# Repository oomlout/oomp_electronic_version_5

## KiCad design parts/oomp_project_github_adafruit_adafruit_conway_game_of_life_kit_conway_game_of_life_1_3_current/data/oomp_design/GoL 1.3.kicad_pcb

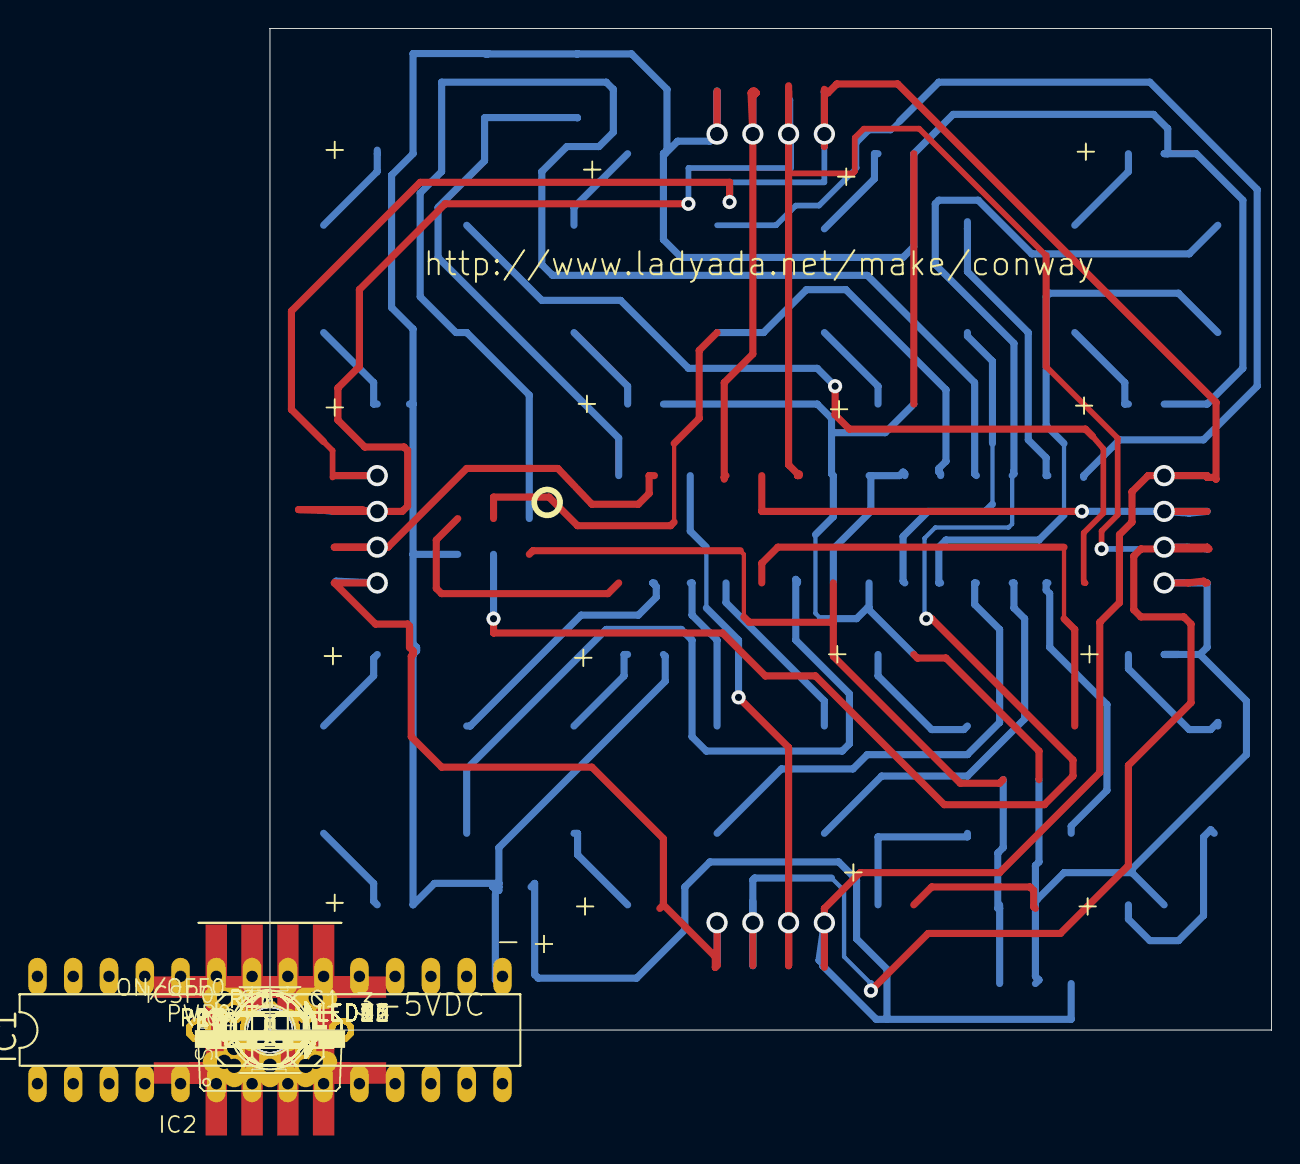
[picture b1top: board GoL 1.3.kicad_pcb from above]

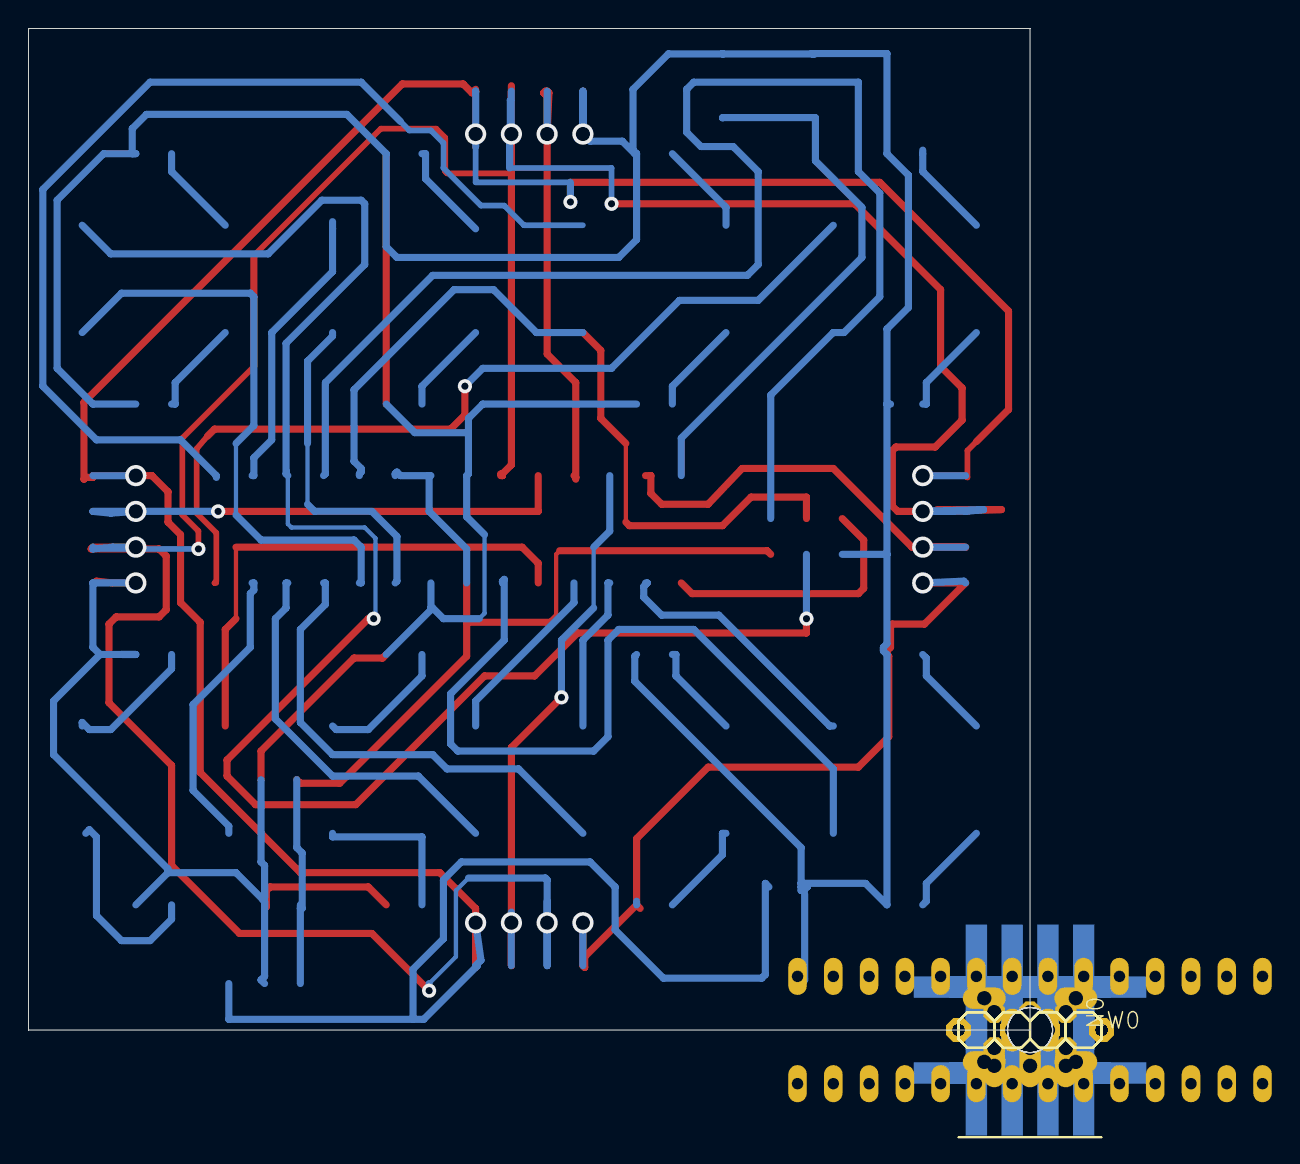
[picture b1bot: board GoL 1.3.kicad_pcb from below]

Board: 16 copper layers, 71.1 x 71.1 mm, 48 parts (2 on the bottom side), 42 nets.

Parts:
C1: 100uF; E2,5-6
C2, C3: 0.1uF; C025-025X050
E0: CONNECT4; http___www.ladyada.net_make_conway_2
IC1: ATMEGA48-10PI; _b_Dual In-line Package__b_ - 28 pin
IC2: LM7805; http___www.ladyada.net_make_conway
ICSP0: 2X03
LED1, LED2, LED3, LED4, LED5, LED6, LED7, LED8, LED9, LED10, LED11, LED12, LED13, LED14, LED15, LED16: LED5MM-EZ
N0: CONNECT4; http___www.ladyada.net_make_conway_2
ON/OFF0: B3F-10XX
PWR0: 1X02
R1, R2, R3, R4, R5, R6, R7, R8, R9, R10, R11, R12, R13, R14, R15, R16: 0207_10
S0: CONNECT4; http___www.ladyada.net_make_conway_2
UNK_HOLE_0: dummyfp0
UNK_HOLE_1: dummyfp1
UNK_HOLE_2: dummyfp2
UNK_HOLE_3: dummyfp3
W0: CONNECT4; http___www.ladyada.net_make_conway_2

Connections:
+5V: C1.+, C3.1, IC1.7, IC1.20, IC1.21, IC2.3, ICSP0.2
BCAST: E0.B3, E0.F3, IC1.23, N0.B2, N0.F2, S0.B3, S0.F3, W0.B2, W0.F2
ERX: E0.B2, E0.F2, IC1.24
GND: C1.-, C2.2, C3.2, E0.B4, E0.F4, IC1.8, IC1.22, IC2.2, ICSP0.6, LED1.K, LED2.K, LED3.K, LED4.K, LED5.K, LED6.K, LED7.K, LED8.K, LED9.K, LED10.K, LED11.K, LED12.K, LED13.K, LED14.K, LED15.K, LED16.K, N0.B4, N0.F4, ON/OFF0.3, ON/OFF0.4, PWR0.2, S0.B4, S0.F4, W0.B4, W0.F4
MISO: IC1.18, ICSP0.1, R5.1
MOSI: IC1.17, ICSP0.4, R4.1
unnamed: LED1.A, R1.2
unnamed: LED2.A, R2.2
unnamed: LED3.A, R3.2
unnamed: LED4.A, R4.2
unnamed: LED5.A, R5.2
unnamed: LED6.A, R6.2
unnamed: LED7.A, R7.2
unnamed: LED8.A, R8.2
unnamed: LED9.A, R9.2
unnamed: LED10.A, R10.2
unnamed: LED11.A, R11.2
unnamed: LED12.A, R12.2
unnamed: LED13.A, R13.2
unnamed: LED14.A, R14.2
unnamed: LED15.A, R15.2
unnamed: LED16.A, R16.2
unnamed: IC1.13, R16.1
unnamed: IC1.12, R15.1
unnamed: IC1.11, R14.1
unnamed: IC1.6, R13.1
unnamed: IC1.5, R12.1
unnamed: IC1.4, R11.1
unnamed: IC1.3, R10.1
unnamed: IC1.2, R9.1
unnamed: IC1.28, ON/OFF0.1, ON/OFF0.2
unnamed: IC1.14, R1.1
unnamed: IC1.15, R2.1
unnamed: IC1.16, R3.1
unnamed: IC1.9, R7.1
unnamed: IC1.10, R8.1
NRX: IC1.25, N0.B3, N0.F3
RESET: IC1.1, ICSP0.5
SCK: IC1.19, ICSP0.3, R6.1
SRX: IC1.26, S0.B2, S0.F2
V+: C2.1, E0.B1, E0.F1, IC2.1, N0.B1, N0.F1, PWR0.1, S0.B1, S0.F1, W0.B1, W0.F1
WRX: IC1.27, W0.B3, W0.F3

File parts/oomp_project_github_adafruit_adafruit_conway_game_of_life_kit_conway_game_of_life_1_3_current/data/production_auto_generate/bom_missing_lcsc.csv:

Designator,Comment,Footprint,OOMP ID,Reason
C1,100uF,"GoL 1.3-import-fps:E2,5-6",,No verified LCSC part number
C2,0.1uF,GoL 1.3-import-fps:C025-025X050,,No verified LCSC part number
C3,0.1uF,GoL 1.3-import-fps:C025-025X050,,No verified LCSC part number
E0,CONNECT4,GoL 1.3-import-fps:http___www.ladyada.net_make_conway_2,,No verified LCSC part number
IC1,ATMEGA48-10PI,GoL 1.3-import-fps:_b_Dual In-line Package__b_ - 28 pin,,No verified LCSC part number
IC2,LM7805,GoL 1.3-import-fps:http___www.ladyada.net_make_conway,,No verified LCSC part number
ICSP0,,GoL 1.3-import-fps:2X03,,No verified LCSC part number
LED1,,GoL 1.3-import-fps:LED5MM-EZ,,No verified LCSC part number
LED2,,GoL 1.3-import-fps:LED5MM-EZ,,No verified LCSC part number
LED3,,GoL 1.3-import-fps:LED5MM-EZ,,No verified LCSC part number
LED4,,GoL 1.3-import-fps:LED5MM-EZ,,No verified LCSC part number
LED5,,GoL 1.3-import-fps:LED5MM-EZ,,No verified LCSC part number
LED6,,GoL 1.3-import-fps:LED5MM-EZ,,No verified LCSC part number
LED7,,GoL 1.3-import-fps:LED5MM-EZ,,No verified LCSC part number
LED8,,GoL 1.3-import-fps:LED5MM-EZ,,No verified LCSC part number
LED9,,GoL 1.3-import-fps:LED5MM-EZ,,No verified LCSC part number
LED10,,GoL 1.3-import-fps:LED5MM-EZ,,No verified LCSC part number
LED11,,GoL 1.3-import-fps:LED5MM-EZ,,No verified LCSC part number
LED12,,GoL 1.3-import-fps:LED5MM-EZ,,No verified LCSC part number
LED13,,GoL 1.3-import-fps:LED5MM-EZ,,No verified LCSC part number
LED14,,GoL 1.3-import-fps:LED5MM-EZ,,No verified LCSC part number
LED15,,GoL 1.3-import-fps:LED5MM-EZ,,No verified LCSC part number
LED16,,GoL 1.3-import-fps:LED5MM-EZ,,No verified LCSC part number
N0,CONNECT4,GoL 1.3-import-fps:http___www.ladyada.net_make_conway_2,,No verified LCSC part number
ON/OFF0,,GoL 1.3-import-fps:B3F-10XX,,No verified LCSC part number
PWR0,,GoL 1.3-import-fps:1X02,,No verified LCSC part number
R1,,GoL 1.3-import-fps:0207_10,,No verified LCSC part number
R2,,GoL 1.3-import-fps:0207_10,,No verified LCSC part number
R3,,GoL 1.3-import-fps:0207_10,,No verified LCSC part number
R4,,GoL 1.3-import-fps:0207_10,,No verified LCSC part number
R5,,GoL 1.3-import-fps:0207_10,,No verified LCSC part number
R6,,GoL 1.3-import-fps:0207_10,,No verified LCSC part number
R7,,GoL 1.3-import-fps:0207_10,,No verified LCSC part number
R8,,GoL 1.3-import-fps:0207_10,,No verified LCSC part number
R9,,GoL 1.3-import-fps:0207_10,,No verified LCSC part number
R10,,GoL 1.3-import-fps:0207_10,,No verified LCSC part number
R11,,GoL 1.3-import-fps:0207_10,,No verified LCSC part number
R12,,GoL 1.3-import-fps:0207_10,,No verified LCSC part number
R13,,GoL 1.3-import-fps:0207_10,,No verified LCSC part number
R14,,GoL 1.3-import-fps:0207_10,,No verified LCSC part number
R15,,GoL 1.3-import-fps:0207_10,,No verified LCSC part number
R16,,GoL 1.3-import-fps:0207_10,,No verified LCSC part number
S0,CONNECT4,GoL 1.3-import-fps:http___www.ladyada.net_make_conway_2,,No verified LCSC part number
W0,CONNECT4,GoL 1.3-import-fps:http___www.ladyada.net_make_conway_2,,No verified LCSC part number

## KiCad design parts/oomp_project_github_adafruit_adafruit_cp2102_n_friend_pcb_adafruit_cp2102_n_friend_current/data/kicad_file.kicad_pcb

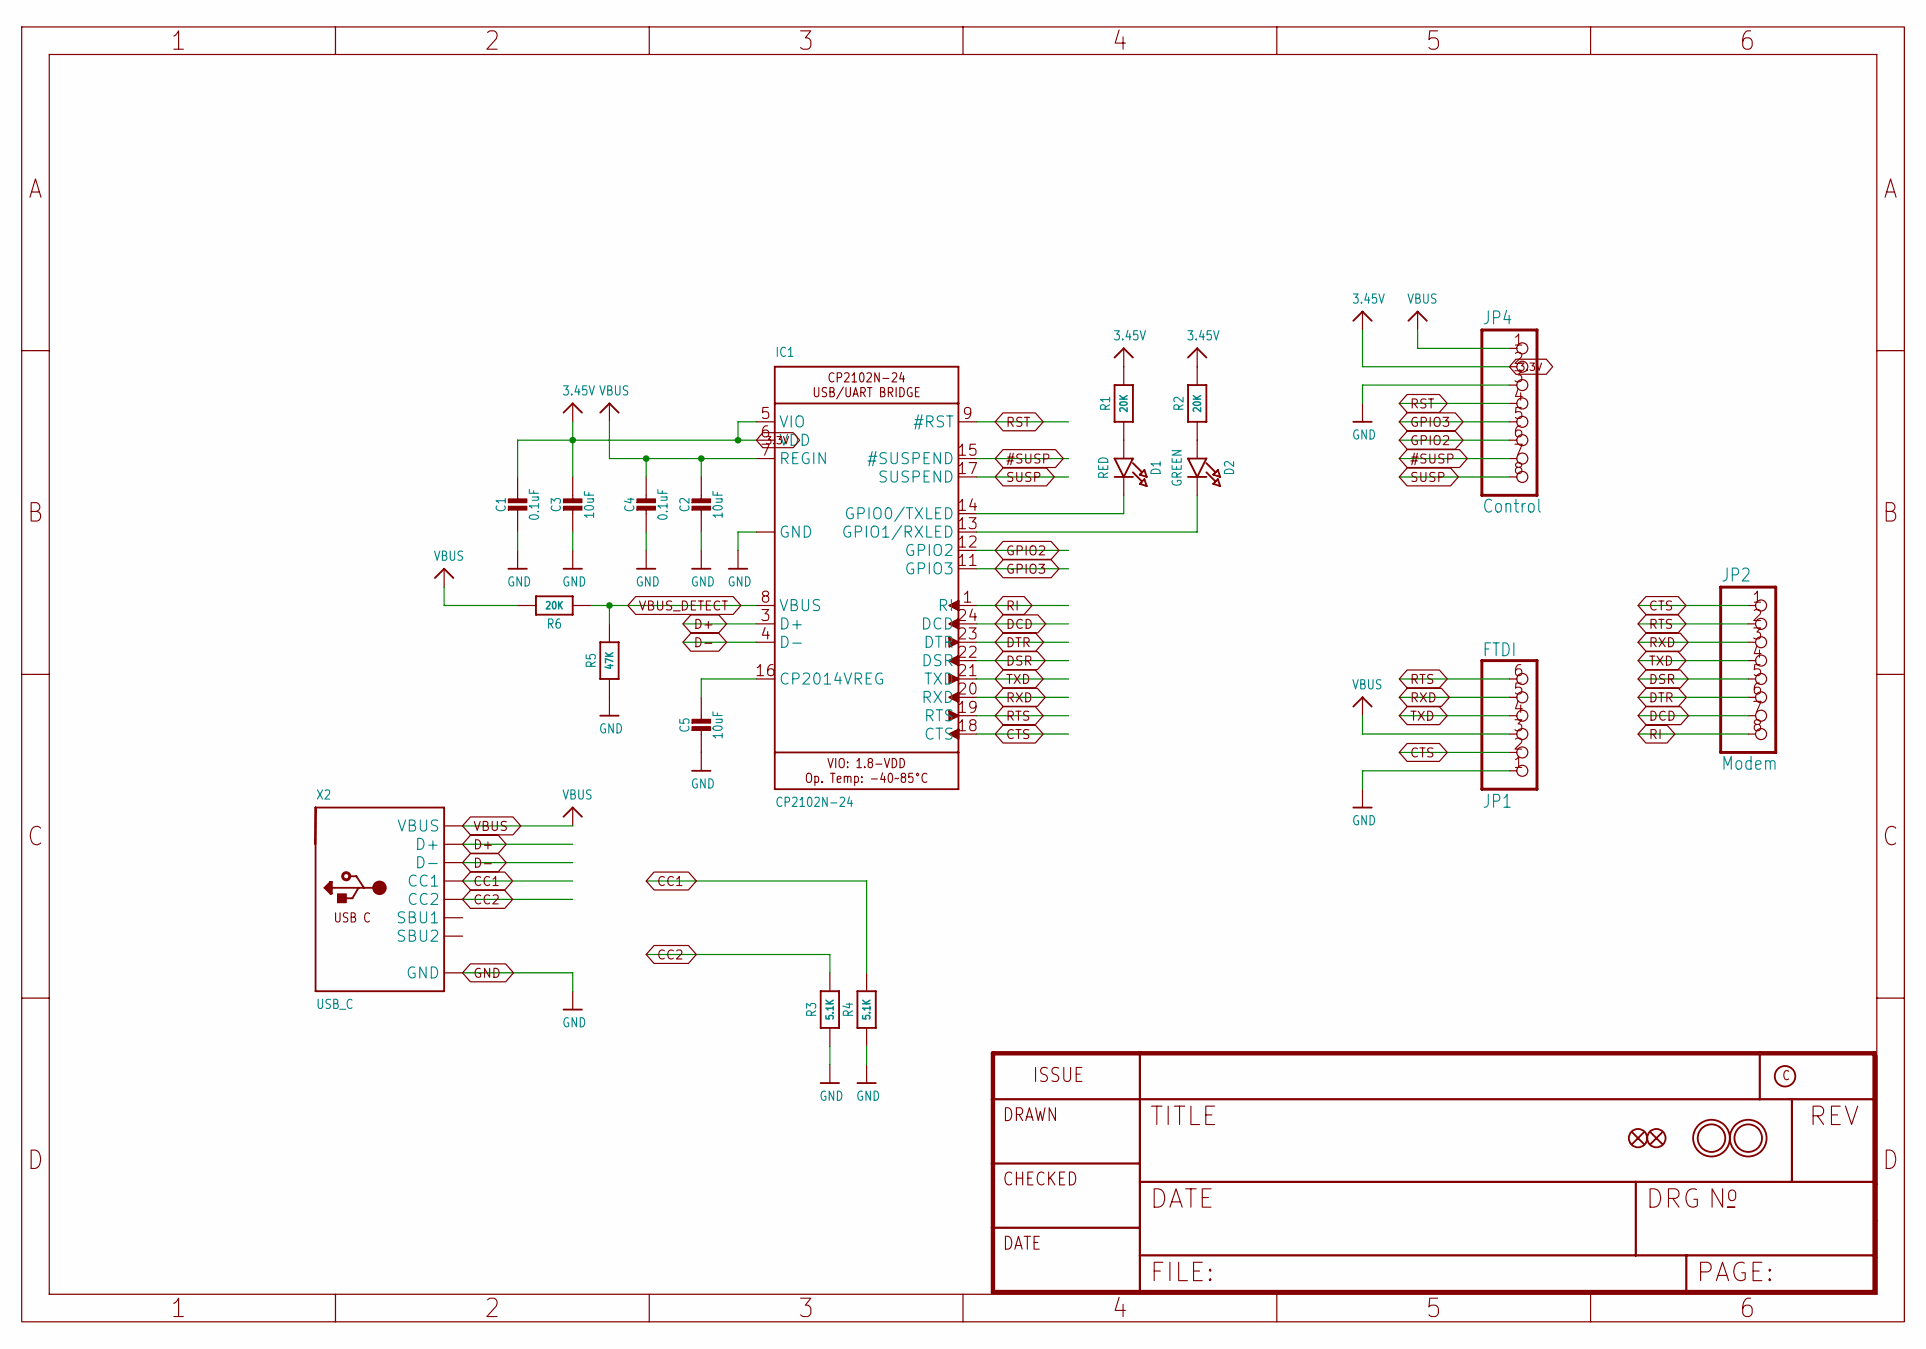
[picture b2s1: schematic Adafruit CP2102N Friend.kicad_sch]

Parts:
C1, C4: 0.1uF; 0603-NO
C2, C3, C5: 10uF; 0805-NO
D1: RED; CHIPLED_0603_NOOUTLINE
D2: GREEN; CHIPLED_0603_NOOUTLINE
FID1, FID2: FIDUCIAL_1MM
IC1: CP2102N-24; QFN24_4MM_SMSC
JP1: FTDI; 1X06_ROUND_76
JP2: Modem; 1X08_ROUND_70
JP4: Control; 1X08_ROUND_70
R1, R2, R6: 20K; 0603-NO
R3, R4: 5.1K; 0603-NO
R5: 47K; 0603-NO
U$18, U$19: MOUNTINGHOLE2.0; MOUNTINGHOLE_2.0_PLATED
X2: USB_C; USB_C_CUSB31-CFM2AX-01-X

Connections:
3.3V: C1.1, C3.1, IC1.5 (VIO), IC1.6 (VDD), JP4.2, R1.2, R2.2
#SUSP: IC1.15 (#SUSPEND), JP4.7
CC1: R4.2, X2.A5 (CC1)
CC2: R3.2, X2.B5 (CC2)
CTS: IC1.18 (CTS), JP1.2, JP2.1
D+: IC1.3 (D+), X2.A6 (D+), X2.B6 (D+)
D-: IC1.4 (D-), X2.A7 (D-), X2.B7 (D-)
DCD: IC1.24 (DCD), JP2.7
DSR: IC1.22 (DSR), JP2.5
DTR: IC1.23 (DTR), JP2.6
GND: C1.2, C2.2, C3.2, C4.2, C5.2, IC1.2 (GND), IC1.THERM (GND), JP1.1, JP4.3, R3.1, R4.1, R5.1, X2.A1B12 (GND), X2.B1A12 (GND)
GPIO2: IC1.12 (GPIO2), JP4.6
GPIO3: IC1.11 (GPIO3), JP4.5
unnamed: D1.A, R1.1
unnamed: C5.1, IC1.16 (CP2014VREG)
unnamed: D2.A, R2.1
unnamed: D1.C, IC1.14 (GPIO0/TXLED)
unnamed: D2.C, IC1.13 (GPIO1/RXLED)
RI: IC1.1 (RI), JP2.8
RST: IC1.9 (#RST), JP4.4
RTS: IC1.19 (RTS), JP1.6, JP2.2
RXD: IC1.20 (RXD), JP1.5, JP2.3
SUSP: IC1.17 (SUSPEND), JP4.8
TXD: IC1.21 (TXD), JP1.4, JP2.4
VBUS: C2.1, C4.1, IC1.7 (REGIN), JP1.3, JP4.1, R6.2, X2.A4B9 (VBUS), X2.B4A9 (VBUS)
VBUS_DETECT: IC1.8 (VBUS), R5.2, R6.1

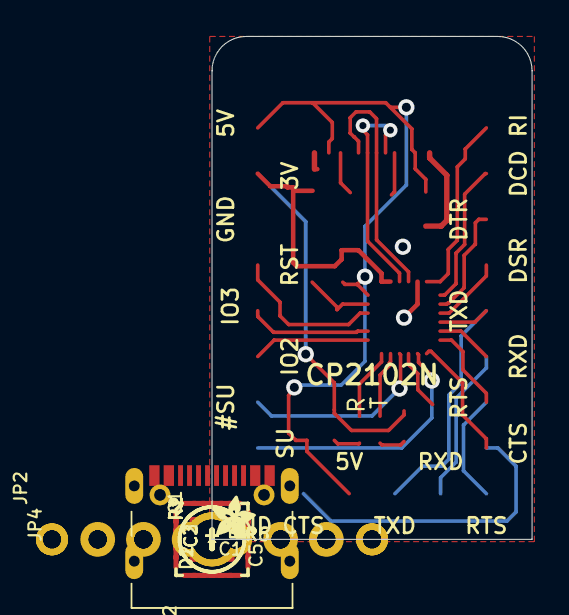
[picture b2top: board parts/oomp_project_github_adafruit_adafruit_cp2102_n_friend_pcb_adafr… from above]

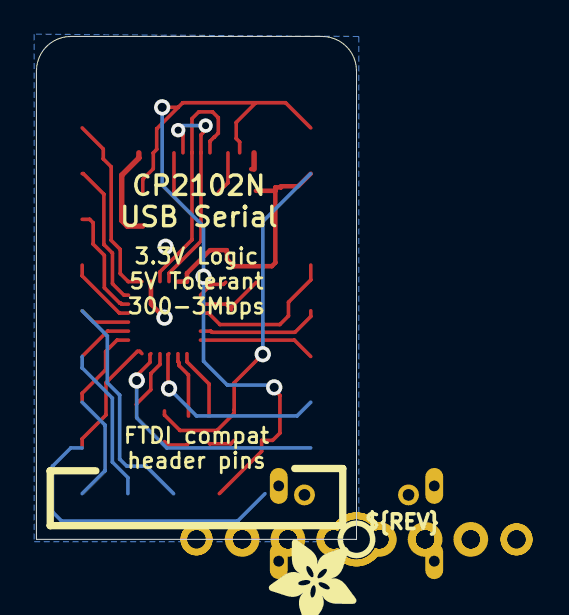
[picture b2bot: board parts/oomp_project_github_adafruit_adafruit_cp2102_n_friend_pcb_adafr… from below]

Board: 2 copper layers, 17.8 x 27.9 mm, 25 parts (2 on the bottom side), 26 nets.

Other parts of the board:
U$8: ADAFRUIT_2.5MM
U$17: PCBFEAT-REV-040
U$22: ADAFRUIT_5MM

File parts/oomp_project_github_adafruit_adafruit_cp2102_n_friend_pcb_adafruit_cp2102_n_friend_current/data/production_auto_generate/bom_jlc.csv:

Comment,Designator,Footprint,LCSC Part #
,U$8,Adafruit CP2102N Friend-import-fps:ADAFRUIT_2.5MM,
,U$22,Adafruit CP2102N Friend-import-fps:ADAFRUIT_5MM,
,U$17,Adafruit CP2102N Friend-import-fps:PCBFEAT-REV-040,
,X2,Adafruit CP2102N Friend-import-fps:USB_C_CUSB31-CFM2AX-01-X,
0.1uF,"C1,C4",Adafruit CP2102N Friend-import-fps:0603-NO,C14663
10uF,"C2,C3,C5",Adafruit CP2102N Friend-import-fps:0805-NO,
20K,"R1,R2,R6",Adafruit CP2102N Friend-import-fps:0603-NO,
47K,R5,Adafruit CP2102N Friend-import-fps:0603-NO,C2907042
5.1K,"R3,R4",Adafruit CP2102N Friend-import-fps:0603-NO,C23186
Control,JP4,Adafruit CP2102N Friend-import-fps:1X08_ROUND_70,C492421
CP2102N-24,IC1,Adafruit CP2102N Friend-import-fps:QFN24_4MM_SMSC,
FTDI,JP1,Adafruit CP2102N Friend-import-fps:1X06_ROUND_76,C37208
GREEN,D2,Adafruit CP2102N Friend-import-fps:CHIPLED_0603_NOOUTLINE,
Modem,JP2,Adafruit CP2102N Friend-import-fps:1X08_ROUND_70,C492421
RED,D1,Adafruit CP2102N Friend-import-fps:CHIPLED_0603_NOOUTLINE,

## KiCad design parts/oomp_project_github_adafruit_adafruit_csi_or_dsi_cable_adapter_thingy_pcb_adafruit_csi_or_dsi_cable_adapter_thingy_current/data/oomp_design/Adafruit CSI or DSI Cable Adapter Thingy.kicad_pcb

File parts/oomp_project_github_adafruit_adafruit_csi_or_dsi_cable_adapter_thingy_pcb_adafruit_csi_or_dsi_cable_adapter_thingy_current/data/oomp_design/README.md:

# OOMP KiCad design copy

Open `Adafruit CSI or DSI Cable Adapter Thingy.kicad_pro` (or the `.kicad_pcb` / `.kicad_sch`) in KiCad. Local OOMP libraries are under `libraries/`. Original inputs are preserved in [../original/](../original/).

Only verified unchanged installed KiCad defaults were renamed. Modified, custom, unmatched and unavailable items remain unchanged. Soldering variants are never swapped during conversion. Existing pad coordinates, nets and UUIDs are preserved.

See [conversion_report.yaml](conversion_report.yaml) for every conversion and skip. Copy this directory before editing; regeneration refuses to overwrite edited design files.

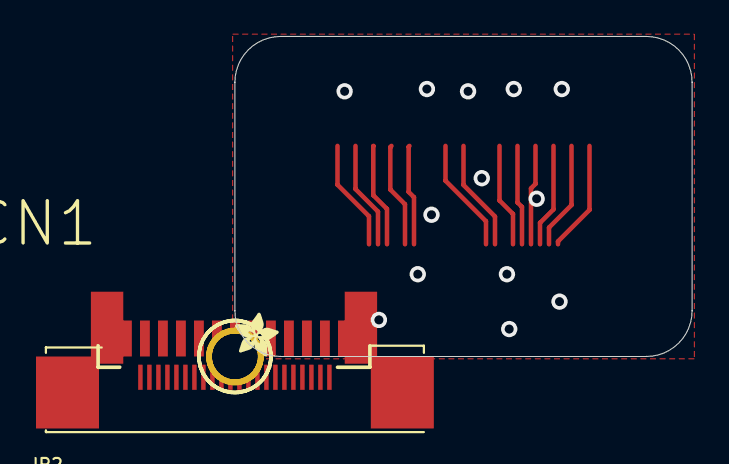
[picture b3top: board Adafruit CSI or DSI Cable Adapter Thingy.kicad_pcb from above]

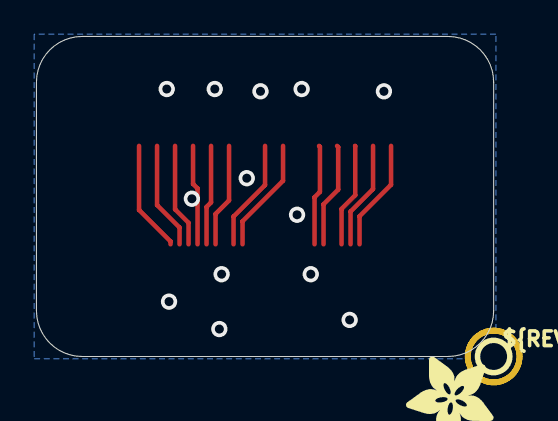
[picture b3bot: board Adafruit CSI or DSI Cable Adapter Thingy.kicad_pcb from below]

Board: 2 copper layers, 25.4 x 17.8 mm, 13 parts (3 on the bottom side), 12 nets.

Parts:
CN1: 22p BOTTOM 0.5mm FPC; FPC_22PIN
FID1, FID2: FIDUCIAL_1MM
JP2: 15p BOTTOM 1mm FPC; FPC_15PIN_1.0MM
PLABEL0: PLABEL0
PLABEL1: PLABEL1
PLABEL2: PLABEL2
PLABEL3: PLABEL3
U$2, U$3: MOUNTINGHOLE2.5; MOUNTINGHOLE_2.5_PLATED
U$4: ADAFRUIT_2.5MM
U$5: ADAFRUIT_5MM
U$6: PCBFEAT-REV-040

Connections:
CAM_3V3: CN1.22, JP2.15
CAM_CK+: CN1.9, JP2.9
CAM_CK-: CN1.8, JP2.8
CAM_D0+: CN1.3, JP2.3
CAM_D0-: CN1.2, JP2.2
CAM_D1+: CN1.6, JP2.6
CAM_D1-: CN1.5, JP2.5
CAM_IO0: CN1.17, JP2.11
CAM_IO1: CN1.18, JP2.12
CAM_SCL: CN1.20, JP2.13
CAM_SDA: CN1.21, JP2.14
GND: CN1.1, CN1.4, CN1.7, CN1.10, CN1.13, CN1.16, CN1.19, JP2.1, JP2.4, JP2.7, JP2.10

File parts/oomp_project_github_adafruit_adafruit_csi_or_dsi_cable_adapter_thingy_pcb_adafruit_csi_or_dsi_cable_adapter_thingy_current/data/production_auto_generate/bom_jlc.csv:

Comment,Designator,Footprint,LCSC Part #
,U$4,Adafruit CSI or DSI Cable Adapter Thingy-import-fps:ADAFRUIT_2.5MM,
,U$5,Adafruit CSI or DSI Cable Adapter Thingy-import-fps:ADAFRUIT_5MM,
,U$6,Adafruit CSI or DSI Cable Adapter Thingy-import-fps:PCBFEAT-REV-040,
,PLABEL0,Adafruit CSI or DSI Cable Adapter Thingy-import-fps:PLABEL0,
,PLABEL1,Adafruit CSI or DSI Cable Adapter Thingy-import-fps:PLABEL1,
,PLABEL2,Adafruit CSI or DSI Cable Adapter Thingy-import-fps:PLABEL2,
,PLABEL3,Adafruit CSI or DSI Cable Adapter Thingy-import-fps:PLABEL3,
15p BOTTOM 1mm FPC,JP2,Adafruit CSI or DSI Cable Adapter Thingy-import-fps:FPC_15PIN_1.0MM,
22p BOTTOM 0.5mm FPC,CN1,Adafruit CSI or DSI Cable Adapter Thingy-import-fps:FPC_22PIN,

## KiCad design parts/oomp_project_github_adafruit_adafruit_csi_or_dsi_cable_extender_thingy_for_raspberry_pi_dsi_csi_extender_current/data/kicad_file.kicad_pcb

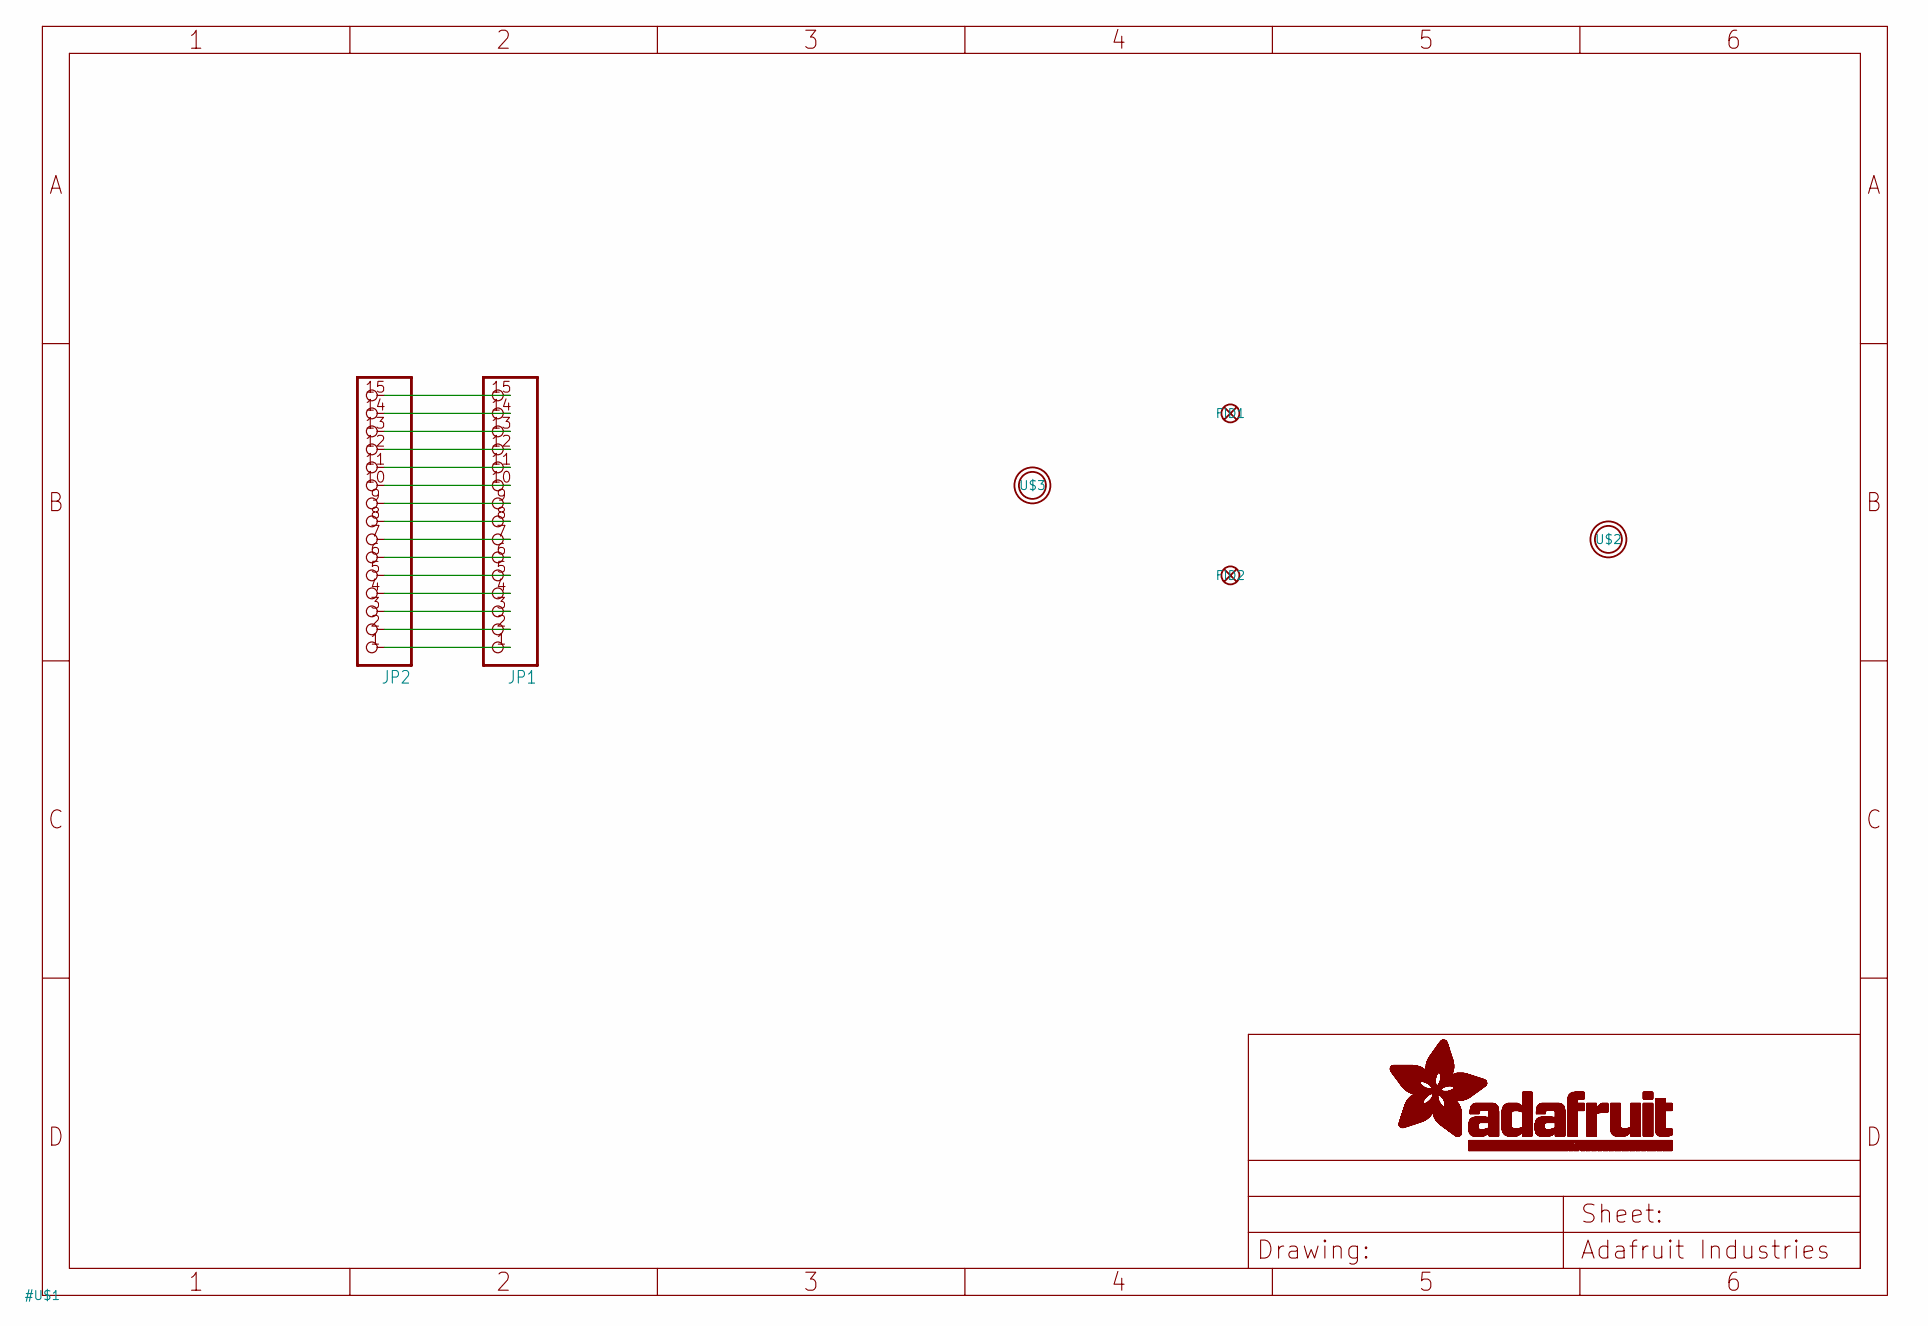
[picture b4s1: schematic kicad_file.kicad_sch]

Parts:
FID1, FID2: FIDUCIAL_1MM
JP1, JP2: HEADER-1X15_FPC1MM_PI; FPC_15PIN_1.0MM
U$2, U$3: MOUNTINGHOLE2.5; MOUNTINGHOLE_2.5_PLATED

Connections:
unnamed: JP1.1, JP2.1
unnamed: JP1.2, JP2.2
unnamed: JP1.3, JP2.3
unnamed: JP1.4, JP2.4
unnamed: JP1.5, JP2.5
unnamed: JP1.6, JP2.6
unnamed: JP1.7, JP2.7
unnamed: JP1.8, JP2.8
unnamed: JP1.9, JP2.9
unnamed: JP1.10, JP2.10
unnamed: JP1.11, JP2.11
unnamed: JP1.12, JP2.12
unnamed: JP1.13, JP2.13
unnamed: JP1.14, JP2.14
unnamed: JP1.15, JP2.15

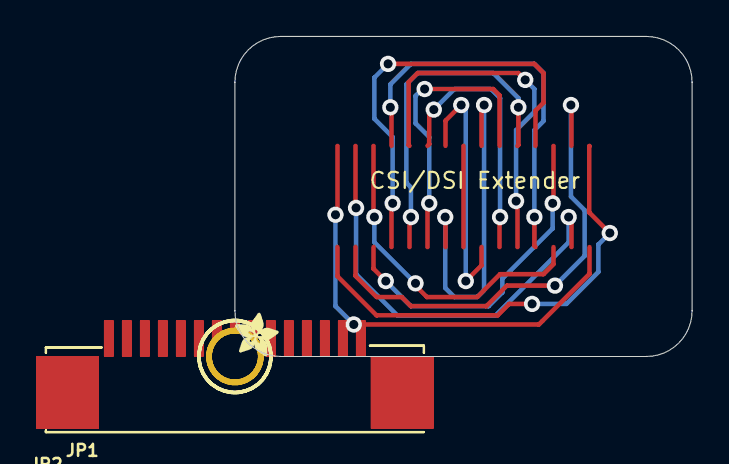
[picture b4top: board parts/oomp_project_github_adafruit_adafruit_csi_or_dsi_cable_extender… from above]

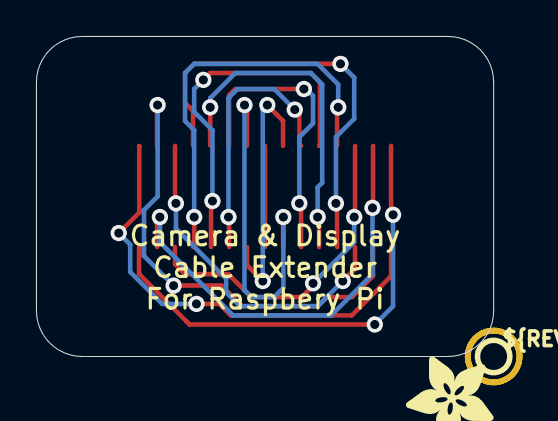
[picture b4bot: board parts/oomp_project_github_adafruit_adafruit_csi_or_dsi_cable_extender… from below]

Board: 2 copper layers, 25.4 x 17.8 mm, 9 parts (2 on the bottom side), 15 nets.

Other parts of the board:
U$4: ADAFRUIT_2.5MM
U$5: ADAFRUIT_5MM
U$6: PCBFEAT-REV-040

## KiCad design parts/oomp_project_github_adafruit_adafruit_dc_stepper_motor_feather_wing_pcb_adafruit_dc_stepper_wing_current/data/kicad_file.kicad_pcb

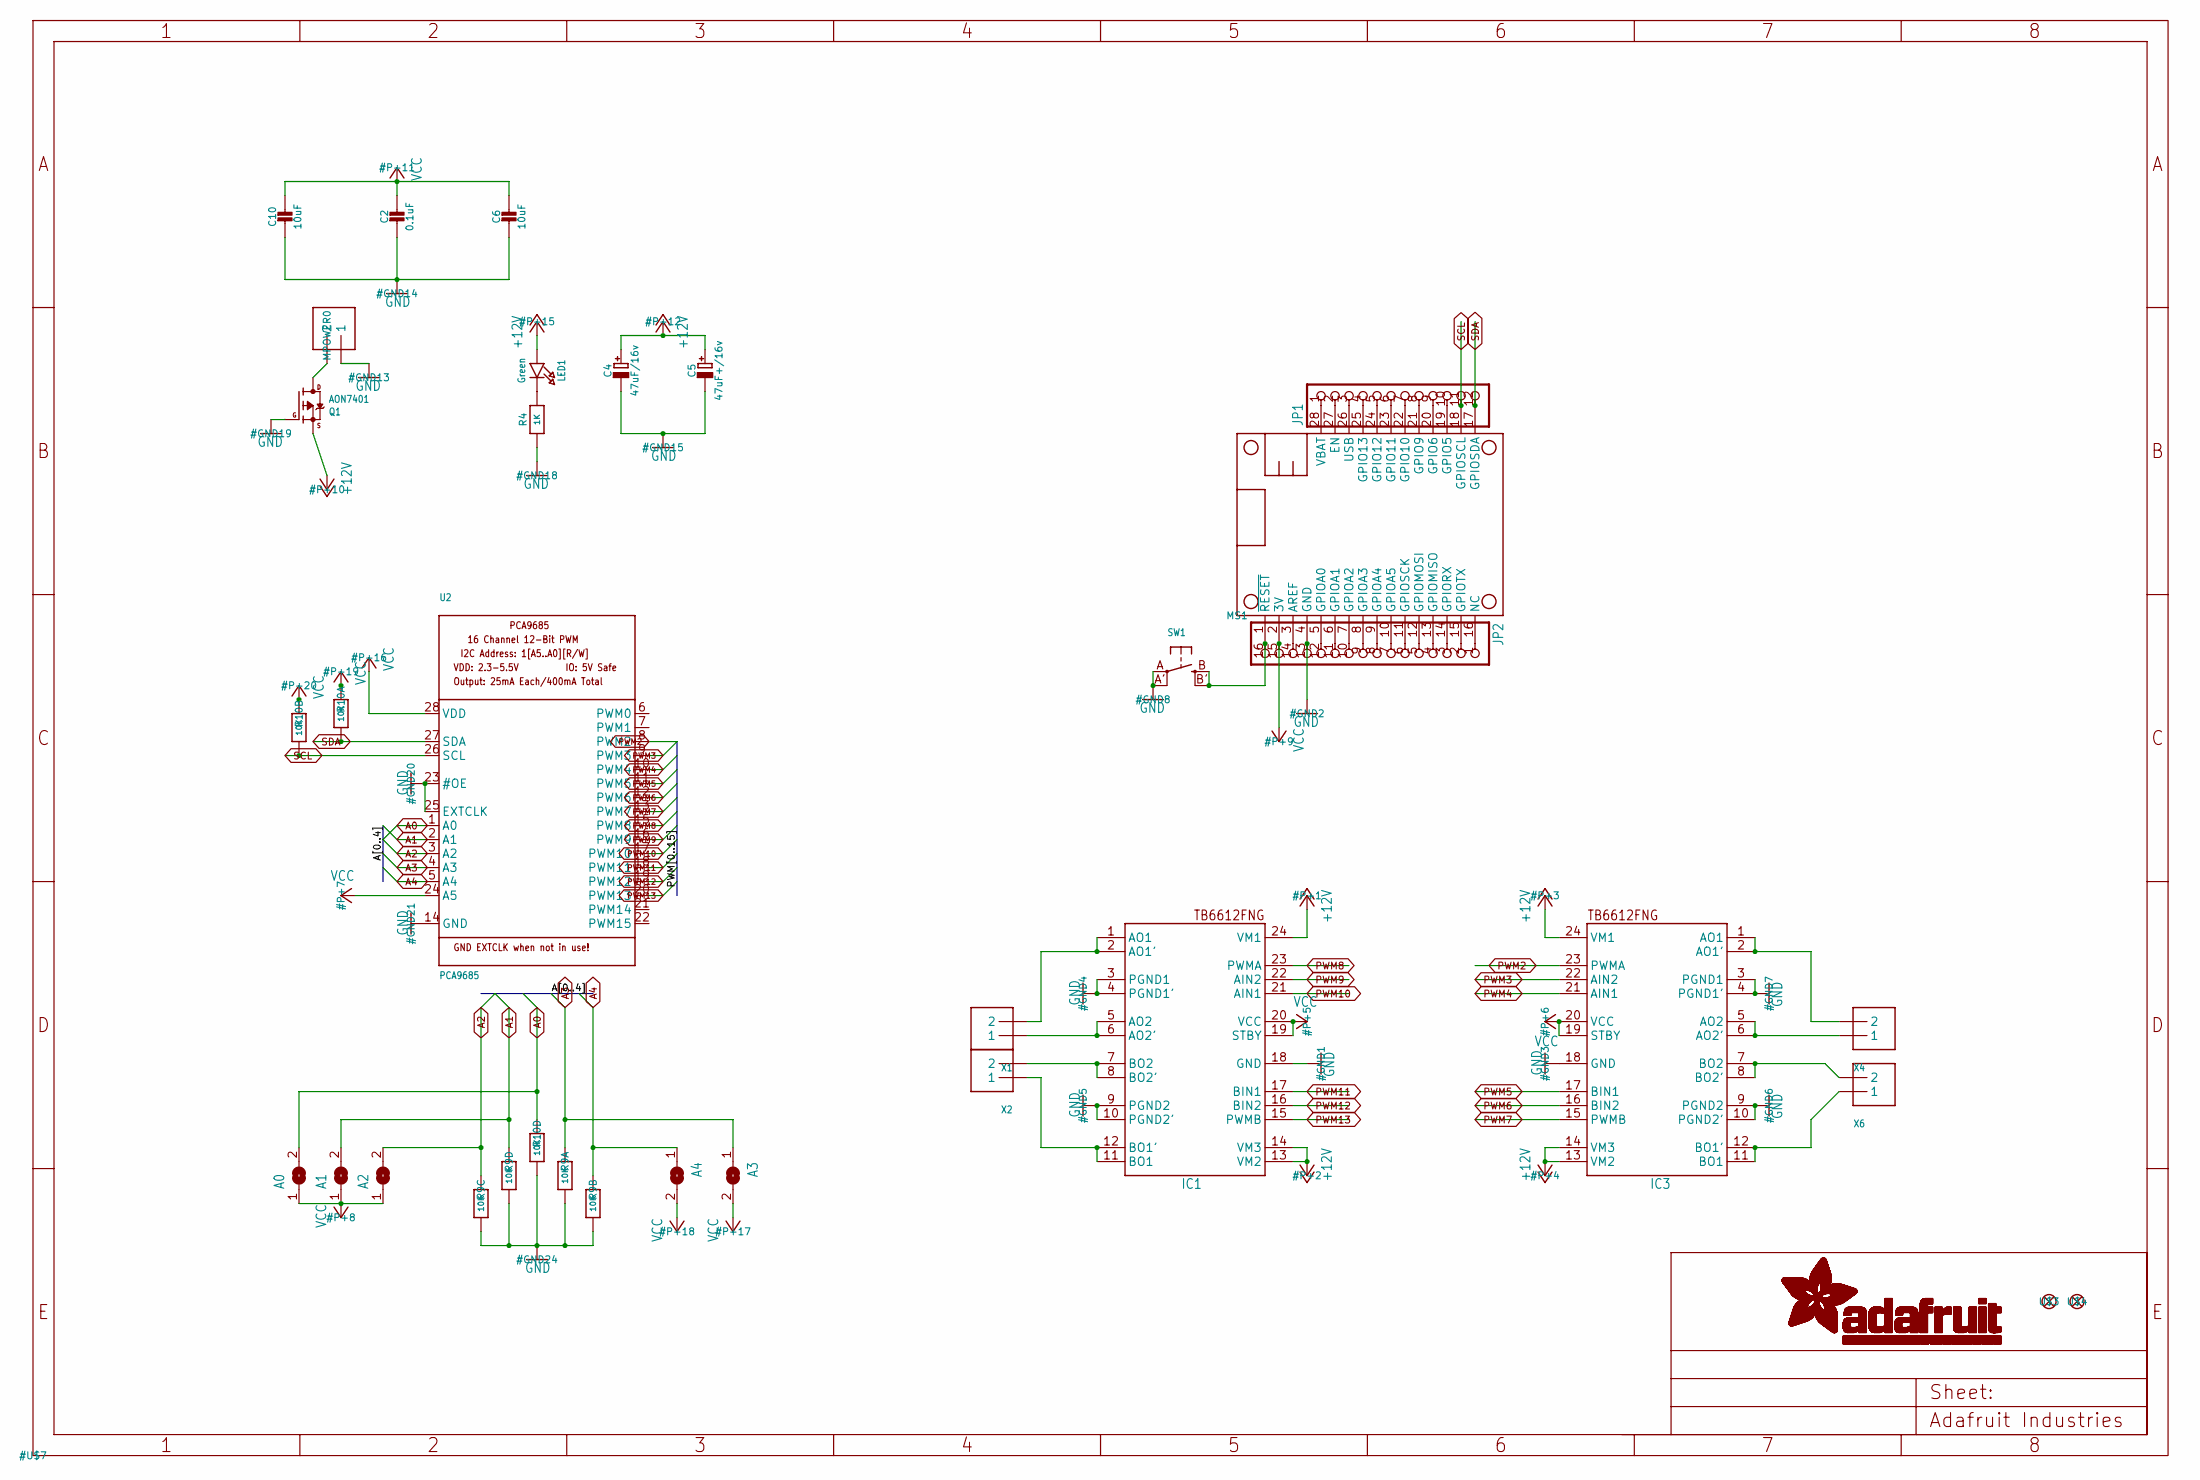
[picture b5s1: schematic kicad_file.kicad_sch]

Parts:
A0, A1, A2, A3, A4: SOLDERJUMPERREFLOW_NOPASTE; SOLDERJUMPER_REFLOW_NOPASTE
C2: 0.1uF; 0805-NO
C4: 47uF/16v; PANASONIC_C
C5: 47uF+/16v; PANASONIC_C
C6, C10: 10uF; 0805-NO
IC1, IC3: TB6612FNG; SSOP24
JP1: HEADER-1X12; 1X12_ROUND
JP2: HEADER-1X16ROUND; 1X16_ROUND
LED1: Green; CHIPLED_0805_NOOUTLINE
MPOWER0: 1X2-3.5MM
MS1: FEATHERWING
Q1: AON7401; POWERDI3333
R4: 1K; 0805-NO
R9, R10: 10K; RESPACK_4X0603
SW1: SWITCH_TACT_SMT4.6X2.8; BTN_KMR2_4.6X2.8
U2: PCA9685; TSSOP28
U$3, U$4: FIDUCIAL""; FIDUCIAL_1MM
X1, X2, X4, X6: TERMBLOCK_1X2; TERMBLOCK_1X2-3.5MM

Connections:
+12V: C4.+, C5.+, IC1.13 (VM2), IC1.14 (VM3), IC1.24 (VM1), IC3.13 (VM2), IC3.14 (VM3), IC3.24 (VM1), LED1.A, Q1.1 (S), Q1.2 (S), Q1.3 (S)
A0: A0.2, R10.4 (1), U2.1 (A0)
A1: A1.2, R9.5 (2), U2.2 (A1)
A2: A2.2, R9.6 (2), U2.3 (A2)
A3: A3.1, R9.8 (2), U2.4 (A3)
A4: A4.1, R9.7 (2), U2.5 (A4)
GND: C2.2, C4.-, C5.-, C6.2, C10.2, IC1.3 (PGND1), IC1.4 (PGND1'), IC1.9 (PGND2), IC1.10 (PGND2'), IC1.18 (GND), IC3.3 (PGND1), IC3.4 (PGND1'), IC3.9 (PGND2), IC3.10 (PGND2'), IC3.18 (GND), JP2.13, MPOWER0.1, MS1.4 (GND), Q1.4 (G), R4.1, R9.1, R9.2 (1), R9.3 (1), R9.4 (1), R10.5 (2), SW1.A, SW1.A' (P1), U2.14 (GND), U2.23 (#OE), U2.25 (EXTCLK)
unnamed: JP1.2, MS1.27 (EN)
unnamed: JP1.4, MS1.25 (GPIO13)
unnamed: MPOWER0.2, Q1.5678 (D)
unnamed: IC1.1 (AO1), IC1.2 (AO1'), X1.2
unnamed: JP1.5, MS1.24 (GPIO12)
unnamed: IC1.5 (AO2), IC1.6 (AO2'), X1.1
unnamed: IC1.7 (BO2), IC1.8 (BO2'), X2.2
unnamed: JP1.6, MS1.23 (GPIO11)
unnamed: IC1.11 (BO1), IC1.12 (BO1'), X2.1
unnamed: JP1.7, MS1.22 (GPIO10)
unnamed: JP1.8, MS1.21 (GPIO9)
unnamed: IC3.1 (AO1), IC3.2 (AO1'), X4.2
unnamed: JP1.9, MS1.20 (GPIO6)
unnamed: IC3.5 (AO2), IC3.6 (AO2'), X4.1
unnamed: IC3.7 (BO2), IC3.8 (BO2'), X6.2
unnamed: JP1.10, MS1.19 (GPIO5)
unnamed: IC3.11 (BO1), IC3.12 (BO1'), X6.1
unnamed: JP2.1, MS1.16 (NC)
unnamed: JP2.2, MS1.15 (GPIOTX)
unnamed: JP2.3, MS1.14 (GPIORX)
unnamed: JP2.4, MS1.13 (GPIOMISO)
unnamed: JP2.5, MS1.12 (GPIOMOSI)
unnamed: JP2.6, MS1.11 (GPIOSCK)
unnamed: JP2.7, MS1.10 (GPIOA5)
unnamed: JP2.8, MS1.9 (GPIOA4)
unnamed: JP2.9, MS1.8 (GPIOA3)
unnamed: JP2.10, MS1.7 (GPIOA2)
unnamed: JP2.11, MS1.6 (GPIOA1)
unnamed: JP2.12, MS1.5 (GPIOA0)
unnamed: JP2.14, MS1.3 (AREF)
unnamed: JP2.16, MS1.1 (~RESET), SW1.B (S), SW1.B' (S1)
unnamed: LED1.C, R4.2
PWM2: IC3.23 (PWMA), U2.8 (PWM2)
PWM3: IC3.22 (AIN2), U2.9 (PWM3)
PWM4: IC3.21 (AIN1), U2.10 (PWM4)
PWM5: IC3.17 (BIN1), U2.11 (PWM5)
PWM6: IC3.16 (BIN2), U2.12 (PWM6)
PWM7: IC3.15 (PWMB), U2.13 (PWM7)
PWM8: IC1.23 (PWMA), U2.15 (PWM8)
PWM9: IC1.22 (AIN2), U2.16 (PWM9)
PWM10: IC1.21 (AIN1), U2.17 (PWM10)
PWM11: IC1.17 (BIN1), U2.18 (PWM11)
PWM12: IC1.16 (BIN2), U2.19 (PWM12)
PWM13: IC1.15 (PWMB), U2.20 (PWM13)
SCL: JP1.11, MS1.18 (GPIOSCL), R10.2 (1), U2.26 (SCL)
SDA: JP1.12, MS1.17 (GPIOSDA), R10.1, U2.27 (SDA)
USB: JP1.3, MS1.26 (USB)
VBAT: JP1.1, MS1.28 (VBAT)
VCC: A0.1, A1.1, A2.1, A3.2, A4.2, C2.1, C6.1, C10.1, IC1.19 (STBY), IC1.20 (VCC), IC3.19 (STBY), IC3.20 (VCC), JP2.15, MS1.2 (3V), R10.7 (2), R10.8 (2), U2.24 (A5), U2.28 (VDD)
